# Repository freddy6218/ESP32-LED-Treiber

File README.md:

# LED-Treiber
ESP32 LED-Treiber

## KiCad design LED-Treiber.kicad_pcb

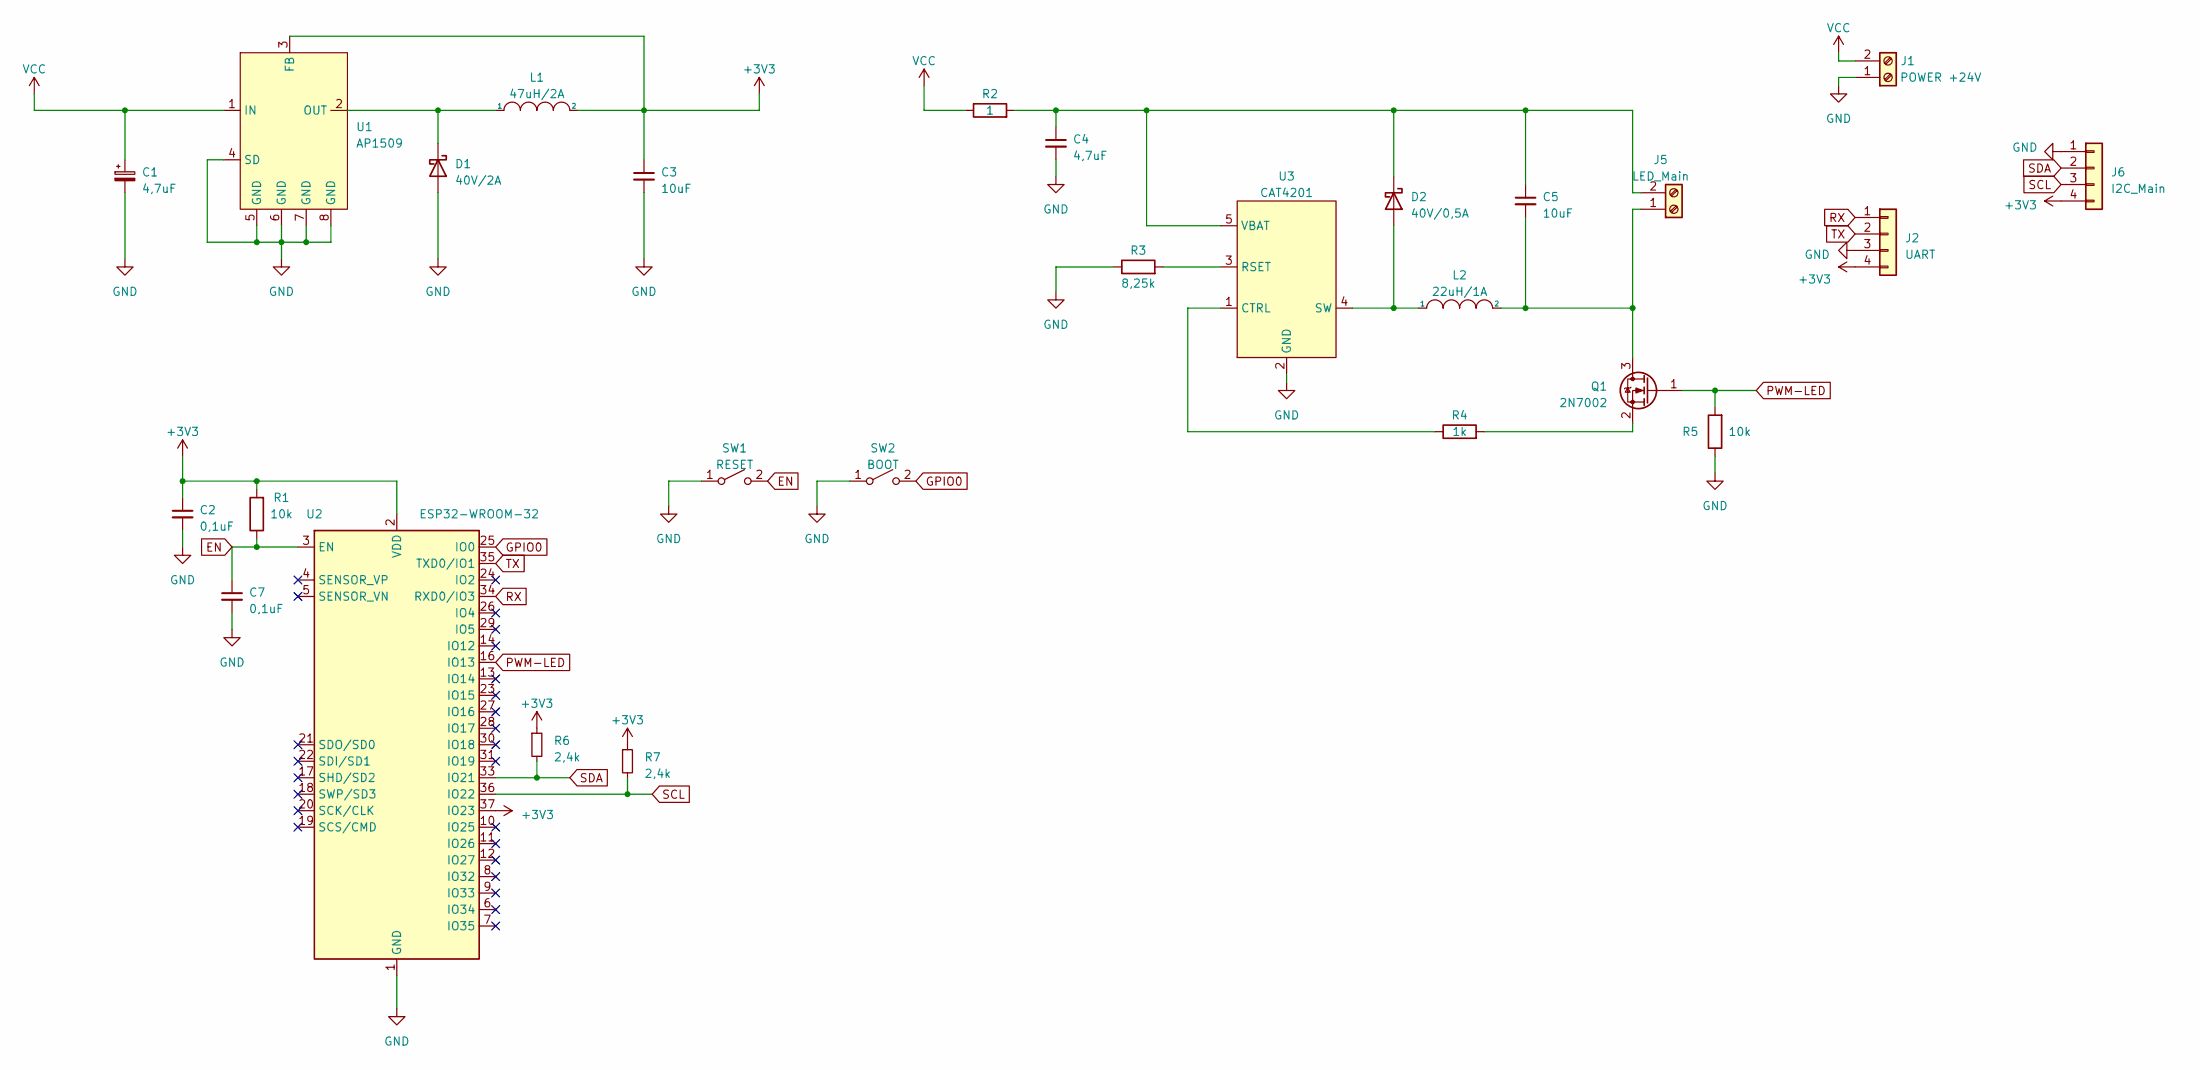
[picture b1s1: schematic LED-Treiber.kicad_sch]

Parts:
C1, C4: 4,7uF; CP_Elec_5x5.3; PARTREV XXX
C2, C7: 0,1uF; C_0603_1608Metric_Pad1.08x0.95mm_HandSolder; PARTREV XXX
C3, C5: 10uF; CP_Elec_5x5.4; PARTREV XXX
D1: 40V/2A; D_SMA_Handsoldering; PARTREV XXX
D2: 40V/0,5A; D_SOD-123; PARTREV XXX
J1: POWER +24V; JST_XH_B2B-XH-A_1x02_P2.50mm_Vertical; PARTREV XXX
J2: UART; JST_XH_B4B-XH-A_1x04_P2.50mm_Vertical; PARTREV XXX
J5: LED_Main; JST_XH_B2B-XH-A_1x02_P2.50mm_Vertical; PARTREV XXX
J6: I2C_Main; JST_XH_B4B-XH-A_1x04_P2.50mm_Vertical; PARTREV XXX
L1: 47uH/2A; HPI1040; PARTREV XXX
L2: 22uH/1A; DJNR5020; PARTREV XXX
Q1: 2N7002; SOT-23; PARTREV XXX
R1, R5: 10k; R_0603_1608Metric_Pad0.98x0.95mm_HandSolder; PARTREV XXX
R2: 1; R_0603_1608Metric_Pad0.98x0.95mm_HandSolder; PARTREV XXX
R3: 8,25k; R_0603_1608Metric_Pad0.98x0.95mm_HandSolder; PARTREV XXX
R4: 1k; R_0603_1608Metric_Pad0.98x0.95mm_HandSolder; PARTREV XXX
R6, R7: 2,4k; R_0603_1608Metric_Pad0.98x0.95mm_HandSolder; PARTREV XXX
SW1: RESET; SW_SPST_FSMSM; PARTREV XXX
SW2: BOOT; SW_SPST_FSMSM; PARTREV XXX
U1: AP1509; SOP-8_3.9x4.9mm_P1.27mm; PARTREV XXX
U2: ESP32-WROOM-32; PARTREV XXX
U3: CAT4201; TSOT-23-5_HandSoldering; PARTREV XXX

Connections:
+3V3: C2.1, C3.1, J2.4, J6.4, L1.2, R1.2, R6.1, R7.1, U1.3 (FB), U2.2 (VDD), U2.37 (IO23)
EN: C7.1, R1.1, SW1.2 (B), U2.3 (EN)
GND: C1.2, C2.2, C3.2, C4.2, C7.2, D1.2 (A), J1.1, J2.3, J6.1, R3.1, R5.1, SW1.1 (A), SW2.1 (A), U1.4 (SD), U1.5 (GND), U1.6 (GND), U1.7 (GND), U1.8 (GND), U2.1 (GND), U2.15 (GND), U2.38 (GND), U2.39 (GND), U3.2 (GND)
GPIO0: SW2.2 (B), U2.25 (IO0)
unnamed: C4.1, C5.1, D2.1 (K), J5.2, R2.2, U3.5 (VBAT)
unnamed: C5.2, J5.1, L2.2, Q1.3 (D)
unnamed: D1.1 (K), L1.1, U1.2 (OUT)
unnamed: D2.2 (A), L2.1, U3.4 (SW)
unnamed: Q1.2 (S), R4.2
unnamed: R3.2, U3.3 (RSET)
unnamed: R4.1, U3.1 (CTRL)
PWM-LED: Q1.1 (G), R5.2, U2.16 (IO13)
RX: J2.1, U2.34 (RXD0/IO3)
SCL: J6.3, R7.2, U2.36 (IO22)
SDA: J6.2, R6.2, U2.33 (IO21)
TX: J2.2, U2.35 (TXD0/IO1)
VCC: C1.1, J1.2, R2.1, U1.1 (IN)

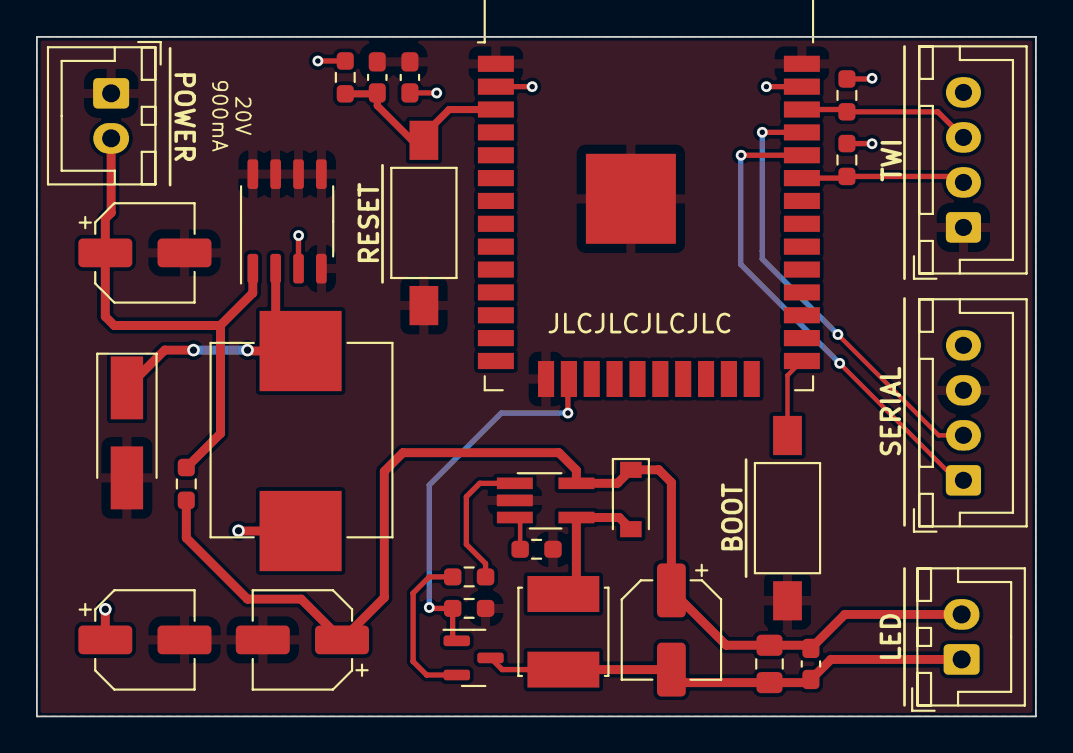
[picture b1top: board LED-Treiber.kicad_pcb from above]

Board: 2 copper layers, 55.5 x 37.8 mm, 27 parts (0 on the bottom side), 17 nets.

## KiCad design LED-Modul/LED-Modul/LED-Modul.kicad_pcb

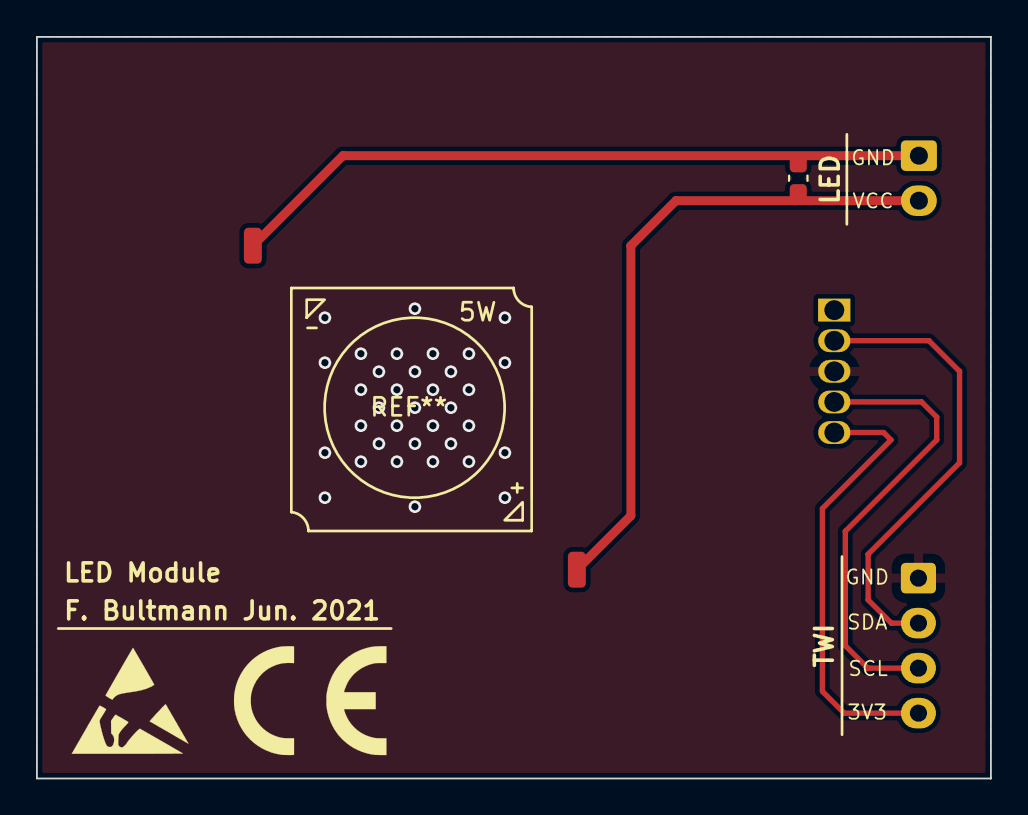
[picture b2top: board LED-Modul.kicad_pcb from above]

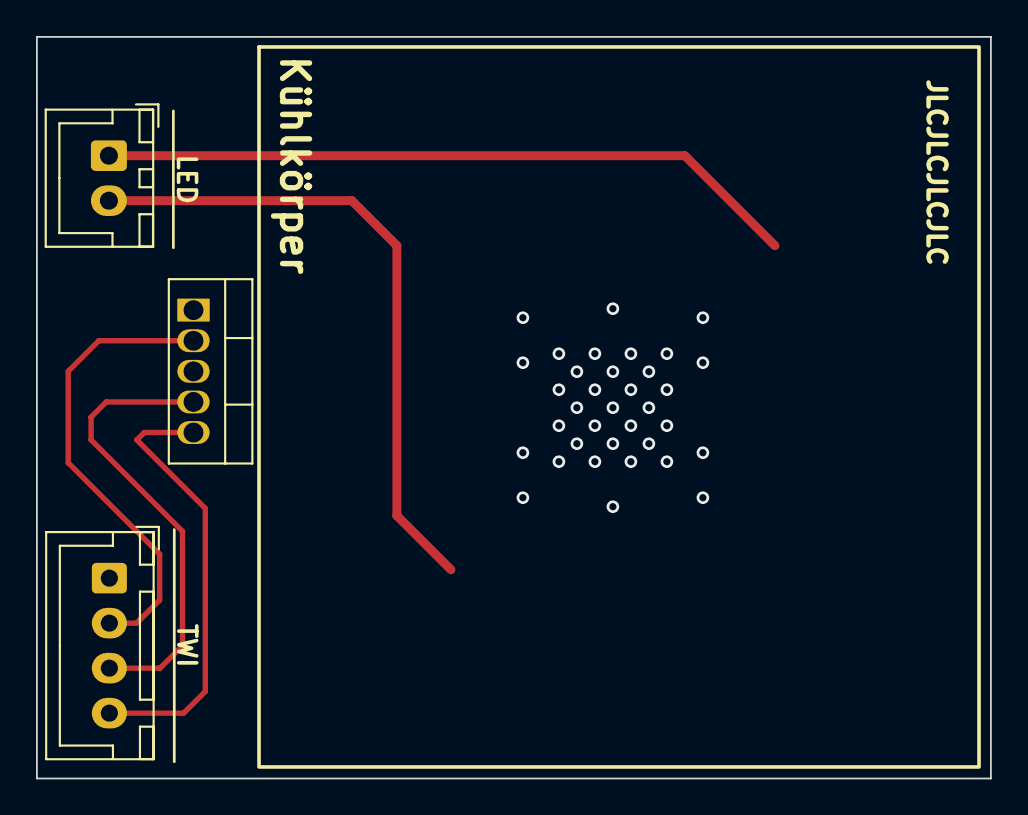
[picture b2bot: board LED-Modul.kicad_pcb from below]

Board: 2 copper layers, 53.0 x 41.2 mm, 3 parts (3 on the bottom side), 4 nets.

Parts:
J1: LED_Mod; JST_XH_B2B-XH-A_1x02_P2.50mm_Vertical
J2: I2C_Mod; JST_XH_B4B-XH-A_1x04_P2.50mm_Vertical
U1: TC74A0-3.3VAT; TO-220-5_Vertical

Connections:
3V3_MOD: J2.4, U1.5 (VDD)
GND: J2.1, U1.3 (GND)
unnamed: J2.2, U1.2 (SDA)
unnamed: J2.3, U1.4 (SCLK)

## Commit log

2021-06-27 init
